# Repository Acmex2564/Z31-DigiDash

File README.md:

# Z31-DigiDash
Reverse Engineering of the 300zx (Z31) Digital Cluster &amp; Design of replacement PCBs

Z31 digital clusters are one of, if not the best examples of this pure 1980s trend. Comprehensive instrumentation, large graphics, and gorgeous VFD illumination were a somewhat expensive option on the 300zx, as well as on Maxima, 240SX, Corvette, Celica/Supra, and a variety of other cars. As the cars languished in the transition period between "late model" and "classic", though, the digital package for the 300zx was not well liked.

It had 3 major issues:

* Terrible update speed
* Lack of brightness
* Unreliability

Now, as Z31s sit at the bottom of the depreciation curve, more people see them as '80s Grand Touring icons and not just as transporation or "sports cars", and a functioning digital dash can be a highlight instead of a detractor.

I have the personal goal of solving at least two of the 3 main problems with these units, by reverse engineering them in the existing state, and designing a drop-on processor board and replacement power supply module. 

See files "Physical Description.md", "Logical Description.md", and "Electrical Description.md" for my observations so far. Also present are images showing how to power up the dash out of the car, and a picture of a printout that I used to map out the input pins.

Note: I am a hobbiest. I am not a EE, CS, Developer, or any related field. Generally, I do my best to read and cargo-cult my way into a working solution. Progress will be slow. The modular design has made it easy to get quick progress and seize control of the actual display, so input, input protection, and power supply will be the main challenges.

Note: None of the boards as-presented are in a state fit to be used without major effort. Big chunks of the Compute-Early-1 design were never tested before I moved on to Compute-Early-2 after component obselecence, etc. and the code to do more than flash the display on the bench was never developed.

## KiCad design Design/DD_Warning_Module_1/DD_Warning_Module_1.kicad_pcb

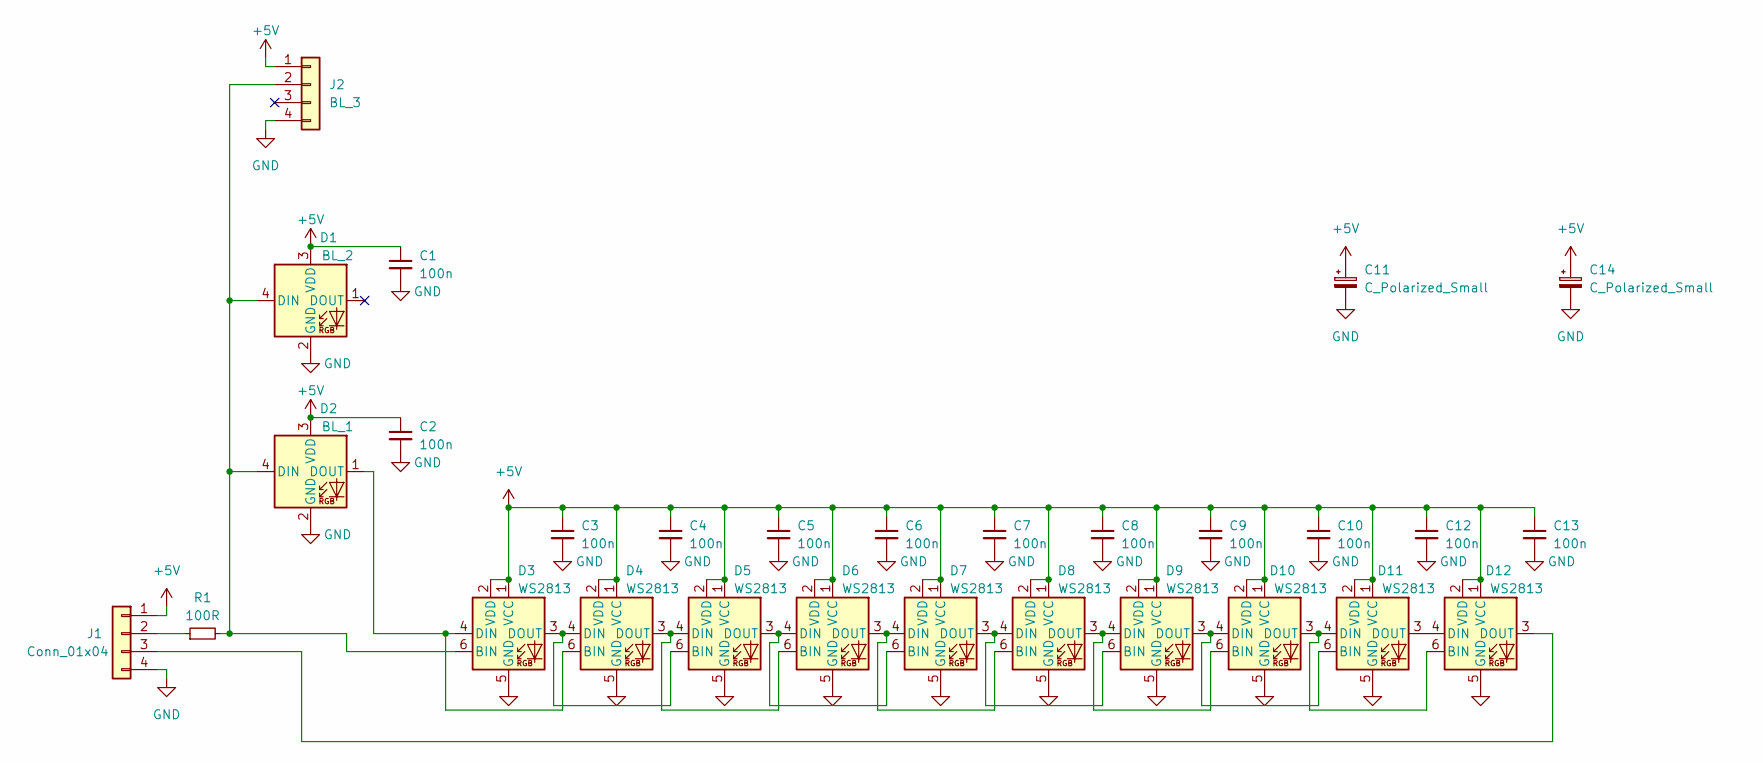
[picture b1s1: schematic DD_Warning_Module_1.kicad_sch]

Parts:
C1, C2, C3, C4, C5, C6, C7, C8, C9, C10, C12, C13: 100n; C_0805_2012Metric_Pad1.18x1.45mm_HandSolder
C11, C14: C_Polarized_Small; CP_Radial_D8.0mm_P2.50mm
D1: BL_2; LED_D5.0mm-4_RGB
D2: BL_1; LED_D5.0mm-4_RGB
D3, D4, D5, D6, D7, D8, D9, D10, D11, D12: WS2813; LED_WS2812_PLCC6_5.0x5.0mm_P1.6mm
J1: Conn_01x04; JST_XH_B4B-XH-A_1x04_P2.50mm_Vertical
J2: BL_3; JST_XH_B4B-XH-A_1x04_P2.50mm_Vertical
R1: 100R; R_0805_2012Metric_Pad1.20x1.40mm_HandSolder

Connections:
+5V: C1.1, C2.1, C3.1, C4.1, C5.1, C6.1, C7.1, C8.1, C9.1, C10.1, C11.1, C12.1, C13.1, C14.1, D1.3 (VDD), D2.3 (VDD), D3.1 (VCC), D3.2 (VDD), D4.1 (VCC), D4.2 (VDD), D5.1 (VCC), D5.2 (VDD), D6.1 (VCC), D6.2 (VDD), D7.1 (VCC), D7.2 (VDD), D8.1 (VCC), D8.2 (VDD), D9.1 (VCC), D9.2 (VDD), D10.1 (VCC), D10.2 (VDD), D11.1 (VCC), D11.2 (VDD), D12.1 (VCC), D12.2 (VDD), J1.1, J2.1
GND: C1.2, C2.2, C3.2, C4.2, C5.2, C6.2, C7.2, C8.2, C9.2, C10.2, C11.2, C12.2, C13.2, C14.2, D1.2 (GND), D2.2 (GND), D3.5 (GND), D4.5 (GND), D5.5 (GND), D6.5 (GND), D7.5 (GND), D8.5 (GND), D9.5 (GND), D10.5 (GND), D11.5 (GND), D12.5 (GND), J1.4, J2.4
unnamed: D1.4 (DIN), D2.4 (DIN), D3.6 (BIN), J2.2, R1.2
unnamed: D2.1 (DOUT), D3.4 (DIN), D4.6 (BIN)
unnamed: D3.3 (DOUT), D4.4 (DIN), D5.6 (BIN)
unnamed: D4.3 (DOUT), D5.4 (DIN), D6.6 (BIN)
unnamed: D5.3 (DOUT), D6.4 (DIN), D7.6 (BIN)
unnamed: D6.3 (DOUT), D7.4 (DIN), D8.6 (BIN)
unnamed: D7.3 (DOUT), D8.4 (DIN), D9.6 (BIN)
unnamed: D8.3 (DOUT), D9.4 (DIN), D10.6 (BIN)
unnamed: D9.3 (DOUT), D10.4 (DIN), D11.6 (BIN)
unnamed: D10.3 (DOUT), D11.4 (DIN), D12.6 (BIN)
unnamed: D11.3 (DOUT), D12.4 (DIN)
unnamed: D12.3 (DOUT), J1.3
unnamed: J1.2, R1.1

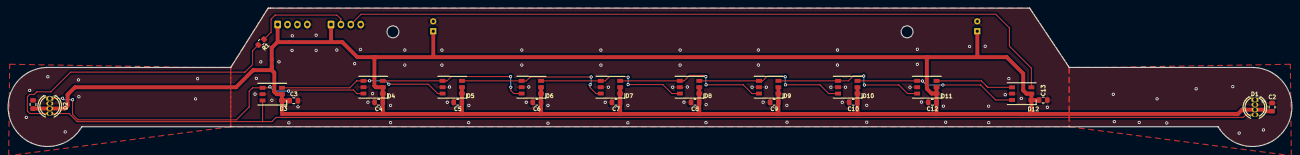
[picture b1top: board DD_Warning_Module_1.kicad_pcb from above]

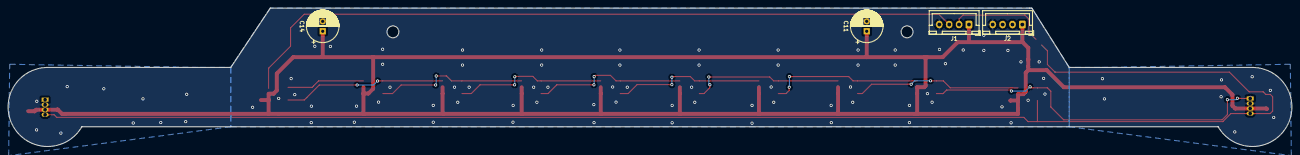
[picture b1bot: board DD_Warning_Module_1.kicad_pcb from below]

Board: 2 copper layers, 324.6 x 35.0 mm, 29 parts (4 on the bottom side), 15 nets.

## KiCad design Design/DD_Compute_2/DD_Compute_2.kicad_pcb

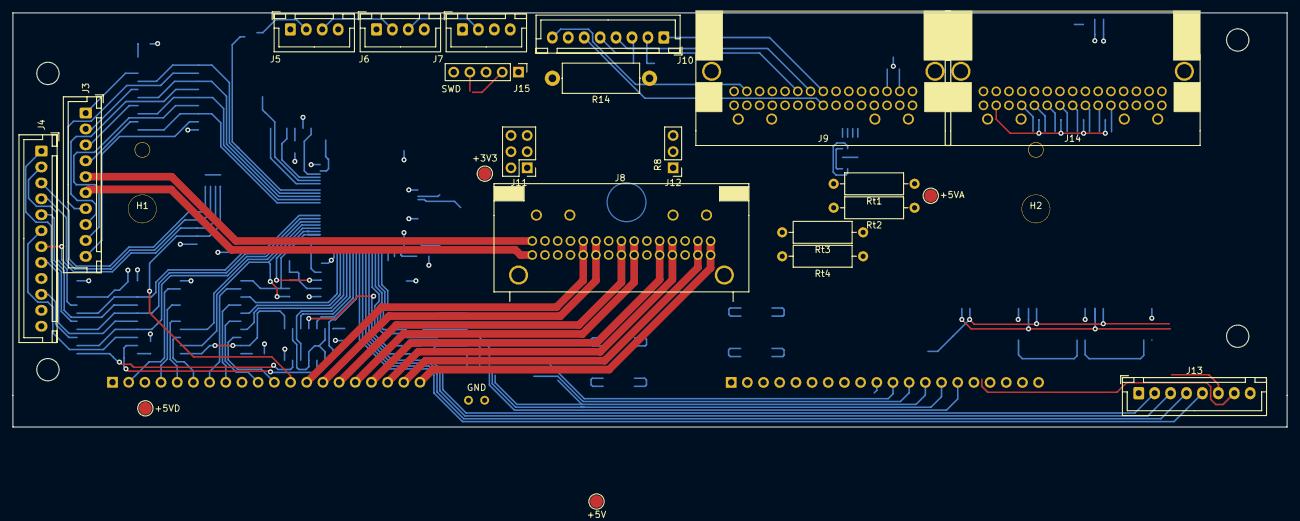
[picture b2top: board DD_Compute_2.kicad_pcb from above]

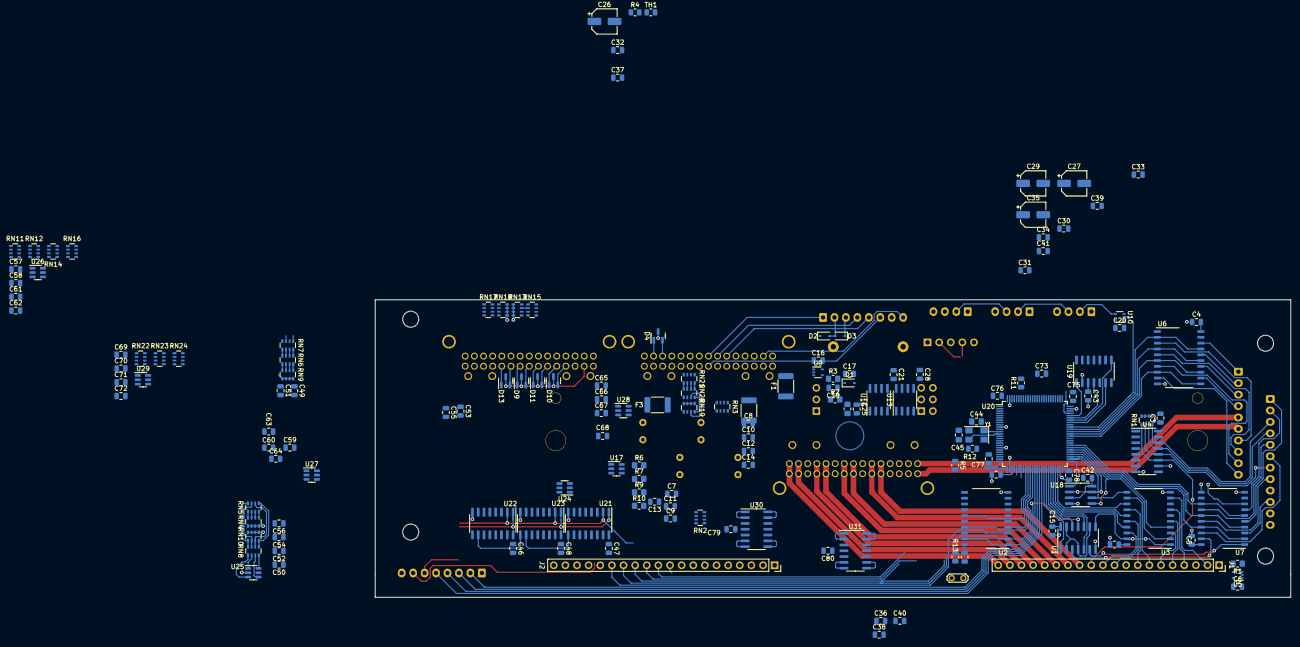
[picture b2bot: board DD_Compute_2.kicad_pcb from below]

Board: 4 copper layers, 200.0 x 65.0 mm, 183 parts (155 on the bottom side), 224 nets.

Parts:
3.3V1: +3V3; TestPoint_Pad_D2.0mm
5V_Analog1: +5VA; TestPoint_Pad_D2.0mm
5V_Disp1: +5VD; TestPoint_Pad_D2.0mm
5V_Logic1: +5V; TestPoint_Pad_D2.0mm
C1, C2, C3, C4, C5, C6, C7, C8, C9, C10, C11, C12, C14, C15, C16, C20, C21, C28, C31, C38, C39, C42, C43, C46, C47, C48, C49, C50, C51, C52, C53, C54, C55, C56, C57, C58, C59, C60, C61, C62, C63, C64, C65, C66, C67, C68, C69, C70, C71, C72, C73, C74, C75, C76, C77, C78, C79, C80: 100nF; C_0805_2012Metric
C13, C17, C19, C25: 10n; C_0805_2012Metric
C26, C27, C29, C35: 47uF; CP_Elec_5x5.3
C30, C32, C34, C36, C37: 1uF; C_0805_2012Metric
C33, C40, C41: 10nF; C_0805_2012Metric
C44, C45: 20pF; C_0805_2012Metric_Pad1.18x1.45mm_HandSolder
D1, D2, D3: 1N4148WS; D_SOD-323
D4: NUP2105L; SOT-23
D9, D10, D11, D13: BAV70; SOT-23
F1, F2, F3: Polyfuse_Small; Fuse_1812_4532Metric_Pad1.30x3.40mm_HandSolder
GND1: GND; TestPoint_2Pads_Pitch2.54mm_Drill0.8mm
H1, H2: Peg; Z31_DD_Mountpeg
H3, H4, H5, H6: Hole; MountingHole_3.5mm
J1: DISP. BOARD CONN 1 (1-20); PinSocket_1x20_P2.54mm_Vertical
J2: DISP. BOARD CONN 2 (21-40); PinSocket_1x20_P2.54mm_Vertical
J3: TRIP BOARD CONN 1 (1-10); JST_XH_B10B-XH-A_1x10_P2.50mm_Vertical
J4: TRIP BOARD CONN 2 (11-22); JST_XH_B12B-XH-A_1x12_P2.50mm_Vertical
J5, J6, J7: Conn_01x03; JST_XH_B4B-XH-A_1x04_P2.50mm_Vertical
J8: POWER SUPPLY - 0349580340; 34958
J9: CAR INTERFACE - 0349610341 - SIG; 349610340
J10: DISP_BOARD_CONN_3; JST_XH_B8B-XH-A_1x08_P2.50mm_Vertical
J11: ISOLATED OUPTUTS & POWER; PinHeader_2x03_P2.54mm_Vertical
J12: ISOLATED INPUTS; PinHeader_1x03_P2.54mm_Vertical
J13: ODOMETER MODULE; JST_XH_B8B-XH-A_1x08_P2.50mm_Vertical
J14: CAR INTERFACE - 0349610341; 349610340
J15: SWD; PinHeader_1x05_P2.54mm_Vertical
R1: 47k; R_0805_2012Metric_Pad1.20x1.40mm_HandSolder
R2: 2.2k; R_0805_2012Metric_Pad1.20x1.40mm_HandSolder
R3, R8: 1k; R_0805_2012Metric_Pad1.20x1.40mm_HandSolder
R4, R5: 47k; R_0805_2012Metric
R6, R9: 75k 1%; R_0805_2012Metric_Pad1.20x1.40mm_HandSolder
R7, R10: 35.7k 1%; R_0805_2012Metric_Pad1.20x1.40mm_HandSolder
R11, R12, R13: 100k; R_0805_2012Metric
R14: 47; R_Axial_DIN0414_L11.9mm_D4.5mm_P15.24mm_Horizontal
RN1, RN2, RN3, RN4, RN5, RN6, RN7, RN8, RN9, RN10, RN11, RN12, RN13, RN14, RN15, RN16, RN17, RN18, RN19, RN20, RN21, RN22, RN23, RN24: 4.7k; R_Array_Convex_4x0603
Rt1, Rt2, Rt3, Rt4: R; R_Axial_DIN0309_L9.0mm_D3.2mm_P12.70mm_Horizontal
TH1: NTCG204AH473JT1; R_0805_2012Metric
U1: 74HCT00D,653; SO-14_3.9x8.65mm_P1.27mm
U2, U3, U6, U7: 74HCT244D,653; SO-20_12.8x7.5mm_P1.27mm
U4, U21, U22, U23: 74HC165D-Q100,118; SOIC-16_3.9x9.9mm_P1.27mm
U5, U9, U10: SN74LV1T34DCK; SOT-353_SC-70-5
U13, U16: VO0631T; SOIC-8_3.9x4.9mm_P1.27mm
U17, U24, U25, U26, U27, U28, U29: SRV05-4; SOT-23-6
U18: 25LC020AT-E/SN; SOIC-8_3.9x4.9mm_P1.27mm
U19: TJR1443; SO-14_3.9x8.65mm_P1.27mm
U20: STM32F103V8Tx; LQFP-100_14x14mm_P0.5mm
U30, U31: LMV324AIDR; SOIC-14_3.9x8.7mm_P1.27mm
Y1: 8MHz; Crystal_SMD_5032-4Pin_5.0x3.2mm

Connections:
12V_Sense: R9.2, R10.1, RN2.2 (R2.1), U17.4 (IO3)
+3V3: 3.3V1.1, C3.1, C21.2, C28.2, C42.2, C46.1, C47.1, C48.1, C73.1, C74.1, C75.1, C76.1, C77.1, C78.1, C79.1, C80.1, J11.2, J15.1, R1.2, R4.1, R12.1, RN1.5 (R4.2), RN1.6 (R3.2), RN1.7 (R2.2), RN1.8 (R1.2), U4.16 (VCC), U13.8 (VCC), U16.8 (VCC), U18.3 (~WP), U18.7 (~HOLD), U18.8 (VCC), U19.5 (Vio), U20.6 (VBAT), U20.11 (VDD), U20.22 (VDDA), U20.28 (VDD), U20.50 (VDD), U20.75 (VDD), U20.100 (VDD), U21.16 (VCC), U22.16 (VCC), U23.16 (VCC), U30.4 (V+), U31.4 (V+)
+5V: 5V_Logic1.1, C1.2, C2.2, C4.2, C5.1, C15.2, C26.1, C29.1, C32.1, C34.1, C43.1, U1.14 (VCC), U2.20 (VCC), U3.20 (VCC), U6.20 (VCC), U7.20 (VCC), U17.5 (VP), U19.3 (Vcc), U24.5 (VP), U25.5 (VP), U26.5 (VP), U27.5 (VP), U28.5 (VP), U29.5 (VP)
+5VA: 5V_Analog1.1, C16.1, C27.1, C30.1, C31.1, C33.1, J9.8, J9.23, J11.3, R3.2, R5.1, R8.2, RN24.3 (R3.1), RN24.4 (R4.1), Rt1.1, Rt2.1, Rt3.1, Rt4.1, U9.5 (VCC)
+5VD: 5V_Disp1.1, C6.1, C20.1, C35.1, C37.1, C39.1, C41.1, J1.3, J2.5, J2.6, J4.9, J5.1, J6.1, J7.1, J8.2, J13.1, U1.2, U1.4, U1.9, U1.13, U5.5 (VCC), U10.5 (VCC)
+12V_ACC_ON: F1.2, J9.4
+12V_CONST: F3.1, J9.1, R9.1
+12V_ON_START: F2.2, J9.3
+12V_ON_START_B: J9.33, J10.8, R14.1
+12V_Security: J9.29, J10.5, RN24.1 (R1.1)
/BOOT0: R11.1, U20.94 (BOOT0)
/CAN_EN: U19.6 (EN), U20.68 (PA9)
/CAN_RX: U19.4 (RXCAN), U20.70 (PA11)
/CAN_TX: U19.1 (TXCAN), U20.71 (PA12)
/DC_ODO: J13.5, U20.41 (PE10)
/Disp_CTL_IC31: J4.6, U7.18 (1Y0)
/Disp_Mode_IC30: J4.10, U7.3 (2Y0)
/Disp_Reset_IC30: J4.1, U7.5 (2Y1)
/Disp_Reset_IC31: J4.8, U7.16 (1Y1)
/Disp_S0_IC30: J3.7, U6.3 (2Y0)
/Disp_S0_IC31: J3.1, U6.18 (1Y0)
/Disp_S1_IC30: J3.8, U6.5 (2Y1)
/Disp_S1_IC31: J3.2, U6.16 (1Y1)
/Disp_S2_IC30: J3.9, U6.7 (2Y2)
/Disp_S2_IC31: J3.3, U6.14 (1Y2)
/Disp_S3_IC30: J3.10, U6.9 (2Y3)
/Disp_S3_IC31: J3.4, U6.12 (1Y3)
/Disp_~WR_IC30: J4.2, U7.7 (2Y2)
/Disp_~WR_IC31: J4.5, U7.14 (1Y2)
/Display_LH_Satellite: J1.10, U3.16 (1Y1)
/Display_SI_Satellite: J1.11, U3.18 (1Y0)
/Display_~CS_Fuel_Lvl: J1.8, U3.14 (1Y2)
/Display_~CS_Fuel_Qty: J1.4, U3.7 (2Y2)
/Display_~CS_Oil: J1.5, U3.5 (2Y1)
/Display_~CS_SpeedGraph: J2.15, U2.3 (2Y0)
/Display_~CS_SpeedNumeric: J2.14, U2.18 (1Y0)
/Display_~CS_TachGraphLoad: J2.12, U2.16 (1Y1)
/Display_~CS_TachGraphRpm: J2.13, U2.5 (2Y1)
/Display_~CS_TachNumeric: J2.11, U2.7 (2Y2)
/Display_~CS_Temp: J1.6, U3.3 (2Y0)
/Display_~CS_Volts: J1.7, U3.12 (1Y3)
/Display_~SCK_Main: J2.16, U2.12 (1Y3)
/Display_~SCK_Satellite: J1.2, U3.9 (2Y3)
/EN_ODO: J13.2, U20.38 (PE7)
/Extra_High_Input: J14.20, RN7.4 (R4.1)
/IC30_OE: U1.1, U20.42 (PE11)
/IC31_OE: U1.5, U20.45 (PE14)
/Illum_Data_Loop1: J5.3, J6.2
/Illum_Data_Loop2: J6.3, J7.2
/Illum_Data_Out: J5.2, U10.4 (Y)
/Indicator_Pilot_Common: J14.5, RN9.5 (R4.2), RN9.6 (R3.2), RN9.7 (R2.2), RN9.8 (R1.2)
/Indicator_Pilot_Left: J14.22, RN7.2 (R2.1)
/Indicator_Pilot_Main: J14.23, RN7.1 (R1.1)
/Indicator_Pilot_Right: J14.21, RN7.3 (R3.1)
/RESET_ODO: J13.4, U20.40 (PE9)
/SPI1_CS0: U2.13 (2A2), U20.33 (PC4)
/SPI1_CS1: U2.15 (2A1), U20.34 (PC5)
/SPI1_CS2/BOOT1: R13.1, U2.2 (1A0), U20.37 (PB2)
/SPI1_CS3: U2.17 (2A0), U20.36 (PB1)
/SPI1_CS4: U2.4 (1A1), U20.35 (PB0)
/SPI1_CS5: U20.29 (PA4), U21.15 (~CE), U22.15 (~CE), U23.15 (~CE)
/SPI1_LH: U21.1 (~PL), U22.1 (~PL), U23.1 (~PL)
/SPI1_MISO: U20.31 (PA6), U22.9 (Q7)
/SPI1_MOSI: J13.7, U20.32 (PA7)
/SPI1_SCK: J13.6, U2.8 (1A3), U20.30 (PA5), U21.2 (CP), U22.2 (CP), U23.2 (CP)
/SPI2_CS0: U3.13 (2A2), U20.48 (PB11)
/SPI2_CS1: U3.15 (2A1), U20.47 (PB10)
/SPI2_CS2: U3.17 (2A0), U20.46 (PE15)
/SWCLK: J15.4, U20.76 (PA14)
/SWDIO: J15.2, U20.72 (PA13)
/Secondary_Warning_Input/ASCD_CruiseB: C66.2, RN19.7 (R2.2), RN20.7 (R2.2), U22.4 (D5), U28.4 (IO3)
/Secondary_Warning_Input/ASCD_OnB: C65.2, RN19.8 (R1.2), RN20.8 (R1.2), U22.3 (D4), U28.6 (IO4)
/Secondary_Warning_Input/ASCD_Set_Disp_1B: C67.2, RN19.6 (R3.2), RN20.6 (R3.2), U22.5 (D6), U28.1 (IO1)
/Secondary_Warning_Input/ASCD_Set_Disp_2B: C68.2, RN19.5 (R4.2), RN20.5 (R4.2), U22.6 (D7), U28.3 (IO2)
/Secondary_Warning_Input/Belt: C50.2, RN8.1 (R1.1), U23.11 (D0), U25.3 (IO2)
/Secondary_Warning_Input/Brake_1: C54.2, RN8.3 (R3.1), U23.13 (D2), U25.4 (IO3)
/Secondary_Warning_Input/Brake_2: C56.2, RN8.4 (R4.1), U23.14 (D3), U25.6 (IO4)
/Secondary_Warning_Input/Coolant: C57.2, RN14.8 (R1.2), U23.3 (D4), U26.3 (IO2)
/Secondary_Warning_Input/Door: C62.2, RN14.5 (R4.2), U23.6 (D7), U26.6 (IO4)
/Secondary_Warning_Input/Extra_HighB: C55.2, RN6.5 (R4.2), RN9.4 (R4.1), U21.3 (D4), U24.3 (IO2)
/Secondary_Warning_Input/Extra_Low_1B: C59.2, RN17.1 (R1.1), U21.11 (D0), U27.3 (IO2)
/Secondary_Warning_Input/Extra_Low_2B: C60.2, RN17.2 (R2.1), U21.12 (D1), U27.1 (IO1)
/Secondary_Warning_Input/Extra_Low_3B: C63.2, RN17.3 (R3.1), U21.13 (D2), U27.4 (IO3)
/Secondary_Warning_Input/Extra_Low_4B: C64.2, RN17.4 (R4.1), U21.14 (D3), U27.6 (IO4)
/Secondary_Warning_Input/Headlamp: C58.2, RN14.7 (R2.2), U23.4 (D5), U26.1 (IO1)
/Secondary_Warning_Input/Left_Turn: C51.2, RN6.7 (R2.2), RN9.2 (R2.1), U21.6 (D7), U24.4 (IO3)
/Secondary_Warning_Input/Main_Beam: C49.2, RN6.8 (R1.2), RN9.1 (R1.1), U21.5 (D6), U24.6 (IO4)
/Secondary_Warning_Input/Right_Turn: C53.2, RN6.6 (R3.2), RN9.3 (R3.1), U21.4 (D5), U24.1 (IO1)
/Secondary_Warning_Input/Sensor: C52.2, RN8.2 (R2.1), U23.12 (D1), U25.1 (IO1)
/Secondary_Warning_Input/Taillamp: C61.2, RN14.6 (R3.2), U23.5 (D6), U26.4 (IO3)
/Secondary_Warning_Input/Warn_ChargeB: C70.2, RN23.7 (R2.2), U22.13 (D2), U29.1 (IO1)
/Secondary_Warning_Input/Warn_FuelB: C71.2, RN23.6 (R3.2), U22.12 (D1), U29.4 (IO3)
/Secondary_Warning_Input/Warn_Oil_PressB: C72.2, RN23.5 (R4.2), U22.11 (D0), U29.6 (IO4)
/Secondary_Warning_Input/Warn_SecurityB: C69.2, RN23.8 (R1.2), U22.14 (D3), U29.3 (IO2)
/Trip_Mode/CTL: U7.2 (1A0), U7.17 (2A0), U20.56 (PD9)
/Trip_Reset: U7.4 (1A1), U7.15 (2A1), U20.57 (PD10)
/Trip_S0: U6.2 (1A0), U6.17 (2A0), U20.65 (PC8)
/Trip_S1: U6.4 (1A1), U6.15 (2A1), U20.64 (PC7)
/Trip_S2: U6.6 (1A2), U6.13 (2A2), U20.63 (PC6)
/Trip_S3: U6.8 (1A3), U6.11 (2A3), U20.62 (PD15)
/Trip_~WR: U7.6 (1A2), U7.13 (2A2), U20.58 (PD11)
/Warning-12V-Supply: J14.6, RN4.1 (R1.1), RN4.2 (R2.1), RN4.3 (R3.1), RN4.4 (R4.1), RN11.1 (R1.1), RN11.2 (R2.1), RN11.3 (R3.1), RN11.4 (R4.1), RN13.1 (R1.1), RN13.2 (R2.1), RN13.3 (R3.1), RN13.4 (R4.1)
/Warning_Belt: D9.1 (A), J14.11, RN5.7 (R2.2), RN8.7 (R2.2), RN10.2 (R2.1)
/Warning_Brake: D13.2 (A), J14.10, RN5.6 (R3.2), RN8.6 (R3.2), RN10.3 (R3.1)
/Warning_Brake_2: D13.1 (A), J14.9, RN5.5 (R4.2), RN8.5 (R4.2), RN10.4 (R4.1)
/Warning_Bulb_Check: D9.3 (K), D10.3 (K), D11.3 (K), D13.3 (K), J14.18
/Warning_Coolant: D11.2 (A), J14.14, RN12.8 (R1.2), RN14.1 (R1.1), RN16.1 (R1.1)
/Warning_Door: D10.2 (A), J14.16, RN12.5 (R4.2), RN14.4 (R4.1), RN16.4 (R4.1)
/Warning_Extra_1: J14.26, RN15.8 (R1.2), RN17.8 (R1.2), RN18.1 (R1.1)
/Warning_Extra_2: J14.27, RN15.7 (R2.2), RN17.7 (R2.2), RN18.2 (R2.1)
/Warning_Extra_3: J14.28, RN15.6 (R3.2), RN17.6 (R3.2), RN18.3 (R3.1)
/Warning_Extra_4: J14.29, RN15.5 (R4.2), RN17.5 (R4.2), RN18.4 (R4.1)
/Warning_Headlamp: D11.1 (A), J14.13, RN12.7 (R2.2), RN14.2 (R2.1), RN16.2 (R2.1)
/Warning_Sensor: D9.2 (A), J14.12, RN5.8 (R1.2), RN8.8 (R1.2), RN10.1 (R1.1)
/Warning_Taillamp: D10.1 (A), J14.15, RN12.6 (R3.2), RN14.3 (R3.1), RN16.3 (R3.1)
/~CAN_ERR: U19.8 (~ERR), U20.69 (PA10)
/~CAN_STB: U19.14 (~STB_N), U20.67 (PA8)
/~CS_ODO: J13.3, U20.39 (PE8)
/~Disp_BI: J1.1, U5.4 (Y)
/~RESET: J15.5, R12.2, U20.14 (NRST)
ASCD_Cruise: J9.13, RN21.3 (R3.1)
ASCD_On: J9.12, J10.6, RN21.4 (R4.1)
ASCD_Set_Disp_1: J9.14, RN21.2 (R2.1)
ASCD_Set_Disp_2: J9.15, RN21.1 (R1.1)
Bias_Grid_Anode: C36.1, C38.1, C40.1, J2.3, J4.11, J8.14, J8.29
Blanking_Control: R1.1, U5.2 (A)
Clock_1_(Time): D4.1 (K), J9.21, U19.13 (CANH)
Clock_2_(Time): D4.2 (K), J9.22, U19.12 (CANL)
Coil_Negative_(Tach): J9.6, J12.2, R2.2
Filament_Fuel_A: J1.19, J8.18, J8.33
Filament_Fuel_B: J1.20, J8.19, J8.34
Filament_Speed_A: J1.17, J8.15, J8.30
Filament_Speed_B: J1.18, J8.16, J8.31
Filament_Sub_A: J1.13, J8.9, J8.24
Filament_Sub_B: J1.14, J8.10, J8.25
Filament_Tach_A: J1.15, J8.12, J8.27
Filament_Tach_B: J1.16, J8.13, J8.28
Filament_Trip_A: J3.5, J8.5
Filament_Trip_B: J3.6, J8.20
Fuel_Gauge_Main: J9.16, RN3.4 (R4.1), Rt1.2
Fuel_Gauge_Sub: J9.17, RN3.3 (R3.1), Rt2.2
Fuel_Injection_Pulse: C19.1, J9.20, J12.3, U13.3 (C2)
Fuel_Injection_Pulse_Protect: J11.5, U13.6 (VO2)
GND: C1.1, C2.1, C3.2, C4.1, C5.2, C6.2, C7.1, C8.1, C9.1, C10.1, C11.1, C12.1, C13.1, C14.1, C15.1, C16.2, C17.2, C20.2, C21.1, C26.2, C27.2, C28.1, C29.2, C30.2, C31.2, C32.2, C33.2, C34.2, C35.2, C36.2, C37.2, C38.2, C39.2, C40.2, C41.2, C42.1, C43.2, C44.2, C45.2, C46.2, C47.2, C48.2, C49.1, C50.1, C51.1, C52.1, C53.1, C54.1, C55.1, C56.1, C57.1, C58.1, C59.1, C60.1, C61.1, C62.1, C63.1, C64.1, C65.1, C66.1, C67.1, C68.1, C69.1, C70.1, C71.1, C72.1, C73.2, C74.2, C75.2, C76.2, C77.2, C78.2, C79.2, C80.2, D1.2 (A), D4.3 (A), GND1.1, J2.1, J2.2, J4.12, J5.4, J6.4, J7.4, J8.1, J8.8, J8.11, J8.17, J8.23, J8.26, J8.32, J9.2, J9.30, J9.32, J10.7, J11.1, J13.8, J15.3, R7.2, R10.2, R11.2, R13.2, RN10.5 (R4.2), RN10.6 (R3.2), RN10.7 (R2.2), RN10.8 (R1.2), RN16.5 (R4.2), RN16.6 (R3.2), RN16.7 (R2.2), RN16.8 (R1.2), RN18.5 (R4.2), RN18.6 (R3.2), RN18.7 (R2.2), RN18.8 (R1.2), RN19.1 (R1.1), RN19.2 (R2.1), RN19.3 (R3.1), RN19.4 (R4.1), RN22.3 (R3.1), RN22.4 (R4.1), TH1.2, U1.7 (GND), U2.10 (GND), U3.10 (GND), U4.3 (D4), U4.4 (D5), U4.5 (D6), U4.6 (D7), U4.8 (GND), U4.10 (DS), U5.3 (GND), U6.10 (GND), U7.8 (1A3), U7.10 (GND), U7.11 (2A3), U9.3 (GND), U10.3 (GND), U13.2 (C1), U13.5 (GND), U16.5 (GND), U17.2 (VN), U18.4 (GND), U19.2 (GND), U20.10 (VSS), U20.19 (VSSA), U20.27 (VSS), U20.49 (VSS), U20.74 (VSS), U20.99 (VSS), U21.8 (GND), U22.8 (GND), U23.8 (GND), U24.2 (VN), U25.2 (VN), U26.2 (VN), U27.2 (VN), U28.2 (VN), U29.2 (VN), U30.11 (V-), U31.11 (V-), Y1.2, Y1.4
INT_TEMP_SENSE: R4.2, TH1.1
Illum_Data: U10.2 (A), U20.66 (PC9)
Illum_Sense: R6.2, R7.1, RN2.3 (R3.1), U17.1 (IO1)
Illumination_2: J9.7, R6.1
Main_Enable: U1.12, U20.43 (PE12)
Manifold_Pressure: J9.11, RN2.4 (R4.1)
unnamed: C17.1, D1.1 (K), R2.1, U13.1 (A1)
unnamed: D2.2 (A), D3.2 (A), J10.2
unnamed: F1.1, J8.3
unnamed: F2.1, J8.4
unnamed: C7.2, RN2.8 (R1.2)
unnamed: C9.2, RN2.7 (R2.2)
unnamed: C11.2, RN2.6 (R3.2)
unnamed: C13.2, RN2.5 (R4.2)
unnamed: C14.2, RN3.8 (R1.2)
unnamed: C12.2, RN3.7 (R2.2)
unnamed: C10.2, RN3.6 (R3.2)
unnamed: C8.2, RN3.5 (R4.2)
unnamed: RN4.8 (R1.2), RN5.1 (R1.1)
unnamed: RN4.7 (R2.2), RN5.2 (R2.1)
unnamed: RN4.6 (R3.2), RN5.3 (R3.1)
unnamed: RN4.5 (R4.2), RN5.4 (R4.1)
unnamed: RN6.1 (R1.1), RN7.8 (R1.2)
unnamed: RN6.2 (R2.1), RN7.7 (R2.2)
unnamed: RN6.3 (R3.1), RN7.6 (R3.2)
unnamed: RN6.4 (R4.1), RN7.5 (R4.2)
unnamed: RN11.8 (R1.2), RN12.1 (R1.1)
unnamed: RN11.7 (R2.2), RN12.2 (R2.1)
unnamed: RN11.6 (R3.2), RN12.3 (R3.1)
unnamed: RN11.5 (R4.2), RN12.4 (R4.1)
unnamed: RN13.8 (R1.2), RN15.1 (R1.1)
unnamed: RN13.7 (R2.2), RN15.2 (R2.1)
unnamed: RN13.6 (R3.2), RN15.3 (R3.1)
unnamed: RN13.5 (R4.2), RN15.4 (R4.1)
unnamed: RN20.1 (R1.1), RN21.8 (R1.2)
unnamed: RN20.2 (R2.1), RN21.7 (R2.2)
unnamed: RN20.3 (R3.1), RN21.6 (R3.2)
unnamed: RN20.4 (R4.1), RN21.5 (R4.2)
unnamed: RN22.5 (R4.2), RN22.8 (R1.2), RN23.1 (R1.1)
unnamed: RN22.2 (R2.1), RN24.7 (R2.2)
unnamed: RN22.6 (R3.2), RN22.7 (R2.2), RN23.2 (R2.1)
unnamed: U1.11, U2.1 (1OE), U2.19 (2OE)
unnamed: U1.8, U3.1 (1OE), U3.19 (2OE)
unnamed: U1.6, U6.1 (1OE), U7.1 (1OE)
unnamed: U1.3, U6.19 (2OE), U7.19 (2OE)
unnamed: C19.2, R3.1, U13.4 (A2)
unnamed: C25.2, R8.1, U16.1 (A1)
unnamed: C44.1, U20.12 (RCC_OSC_IN), Y1.1
unnamed: C45.1, U20.13 (RCC_OSC_OUT), Y1.3
unnamed: U21.9 (Q7), U23.10 (DS)
unnamed: U22.10 (DS), U23.9 (Q7)
unnamed: U30.1, U30.2 (-)
unnamed: U30.6 (-), U30.7
unnamed: U30.8, U30.9 (-)
unnamed: U30.13 (-), U30.14
unnamed: U31.1, U31.2 (-)
unnamed: U31.6 (-), U31.7
unnamed: U31.8, U31.9 (-)
unnamed: U31.13 (-), U31.14
Oil_Pressure: J9.18, RN3.2 (R2.1), Rt3.2
PS_TEMP_SENSE: J8.22, R5.2, RN2.1 (R1.1)
SPI2_CS5: U18.1 (~CS), U20.51 (PB12)
SPI2_LH: U3.4 (1A1), U4.1 (~PL), U20.55 (PD8)
SPI2_MISO: U4.9 (Q7), U18.2 (MISO), U20.53 (PB14)
SPI2_MOSI: U3.2 (1A0), U18.5 (MOSI), U20.54 (PB15)
SPI2_SCK: U3.11 (2A3), U4.2 (CP), U18.6 (SCK), U20.52 (PB13)
SW_Indicated_Spd: J1.12, RN1.1 (R1.1), U4.11 (D0)
SW_MPH-MPG: J4.7, RN1.2 (R2.1), U4.12 (D1)
SW_Trip_A: J4.4, RN1.3 (R3.1), U4.13 (D2)
SW_Trip_B: J4.3, RN1.4 (R4.1), U4.14 (D3)
Satellite_Enable: U1.10, U20.44 (PE13)
Speed_Sensor_In: C25.1, J9.9, J12.1, U16.2 (C1)
Speed_Sensor_Protect: J11.4, U16.7 (VO1)
Speed_Signal_Out: J9.10, U9.4 (Y)
Tach_Protect: J11.6, U13.7 (VO1)
Warning_Charge: D3.1 (K), J9.25, J10.3, R14.2, RN24.2 (R2.1)
Warning_Fuel_Level: D2.1 (K), J9.26, RN23.3 (R3.1), RN24.6 (R3.2)
Warning_Oil_Pressure: J9.27, J10.1, RN23.4 (R4.1), RN24.5 (R4.2)
Warning_Security: J9.28, J10.4, RN22.1 (R1.1), RN24.8 (R1.2)
Water_Temperature: J9.19, RN3.1 (R1.1), Rt4.2

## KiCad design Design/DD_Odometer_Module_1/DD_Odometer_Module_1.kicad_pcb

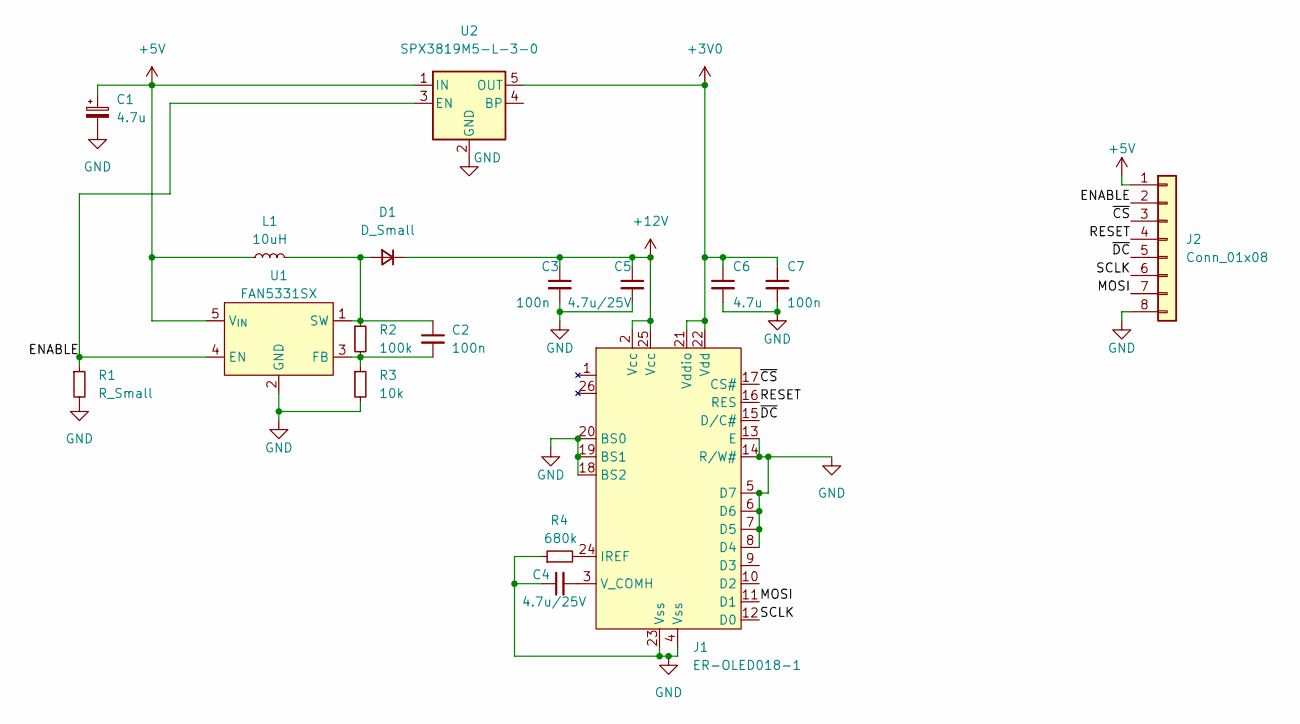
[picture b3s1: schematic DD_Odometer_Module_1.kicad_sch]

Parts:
C1, C6: 4.7u; C_0805_2012Metric_Pad1.18x1.45mm_HandSolder
C2, C3, C7: 100n; C_0805_2012Metric_Pad1.18x1.45mm_HandSolder
C4, C5: 4.7u/25V; C_0805_2012Metric_Pad1.18x1.45mm_HandSolder
D1: D_Small; D_SOD-123
J1: ER-OLED018-1; ER-CON26HT-1
J2: Conn_01x08; JST_XH_B8B-XH-AM_1x08_P2.50mm_Vertical
L1: 10uH; L_1008_2520Metric_Pad1.43x2.20mm_HandSolder
R1: R_Small; R_0805_2012Metric_Pad1.20x1.40mm_HandSolder
R2: 100k; R_0805_2012Metric_Pad1.20x1.40mm_HandSolder
R3: 10k; R_0805_2012Metric_Pad1.20x1.40mm_HandSolder
R4: 680k; R_0805_2012Metric_Pad1.20x1.40mm_HandSolder
U1: FAN5331SX; TSOP-5_1.65x3.05mm_P0.95mm
U2: SPX3819M5-L-3-0; SOT-23-5

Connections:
+3V0: C6.1, C7.1, J1.21 (Vddio), J1.22 (Vdd), U2.5 (OUT)
+5V: C1.1, J2.1, L1.1, U1.5 (V_{IN}), U2.1 (IN)
+12V: C3.1, C5.1, D1.1 (K), J1.2 (Vcc), J1.25 (Vcc)
/ENABLE: J2.2, R1.1, U1.4 (EN), U2.3 (EN)
/MOSI: J1.11 (D1), J2.7
/RESET: J1.16 (RES), J2.4
/SCLK: J1.12 (D0), J2.6
/~CS: J1.17 (CS#), J2.3
/~DC: J1.15 (D/C#), J2.5
GND: C1.2, C3.2, C4.1, C5.2, C6.2, C7.2, J1.4 (Vss), J1.5 (D7), J1.6 (D6), J1.7 (D5), J1.8 (D4), J1.13 (E), J1.14 (R/W#), J1.18 (BS2), J1.19 (BS1), J1.20 (BS0), J1.23 (Vss), J2.8, R1.2, R3.2, R4.1, U1.2 (GND), U2.2 (GND)
unnamed: C2.1, D1.2 (A), L1.2, R2.1, U1.1 (SW)
unnamed: C2.2, R2.2, R3.1, U1.3 (FB)
unnamed: C4.2, J1.3 (V_COMH)
unnamed: J1.24 (IREF), R4.2

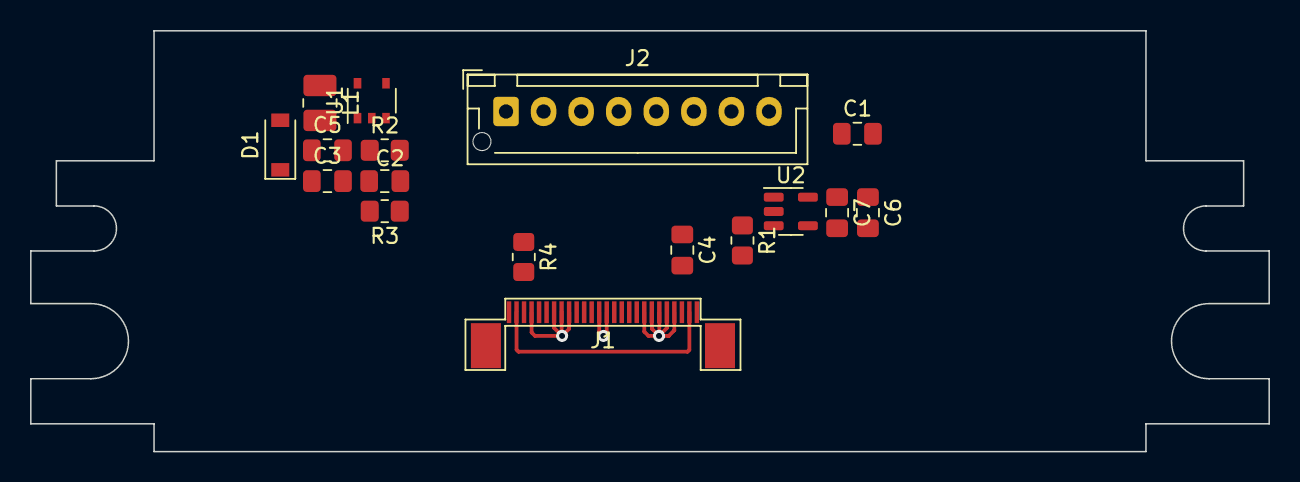
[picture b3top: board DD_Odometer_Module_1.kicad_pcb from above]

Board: 2 copper layers, 82.4 x 28.0 mm, 17 parts (0 on the bottom side), 14 nets.

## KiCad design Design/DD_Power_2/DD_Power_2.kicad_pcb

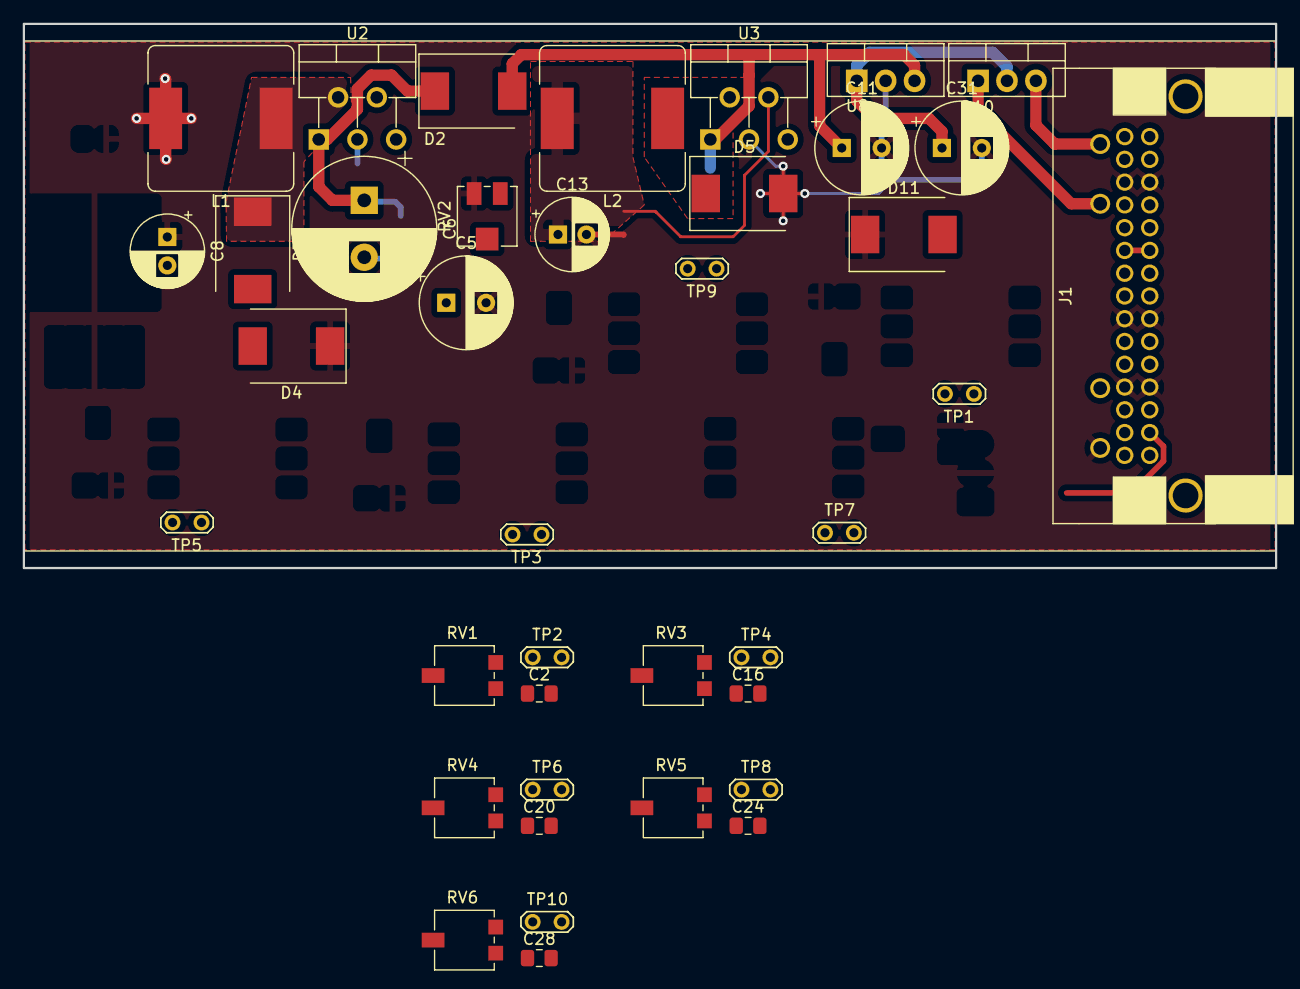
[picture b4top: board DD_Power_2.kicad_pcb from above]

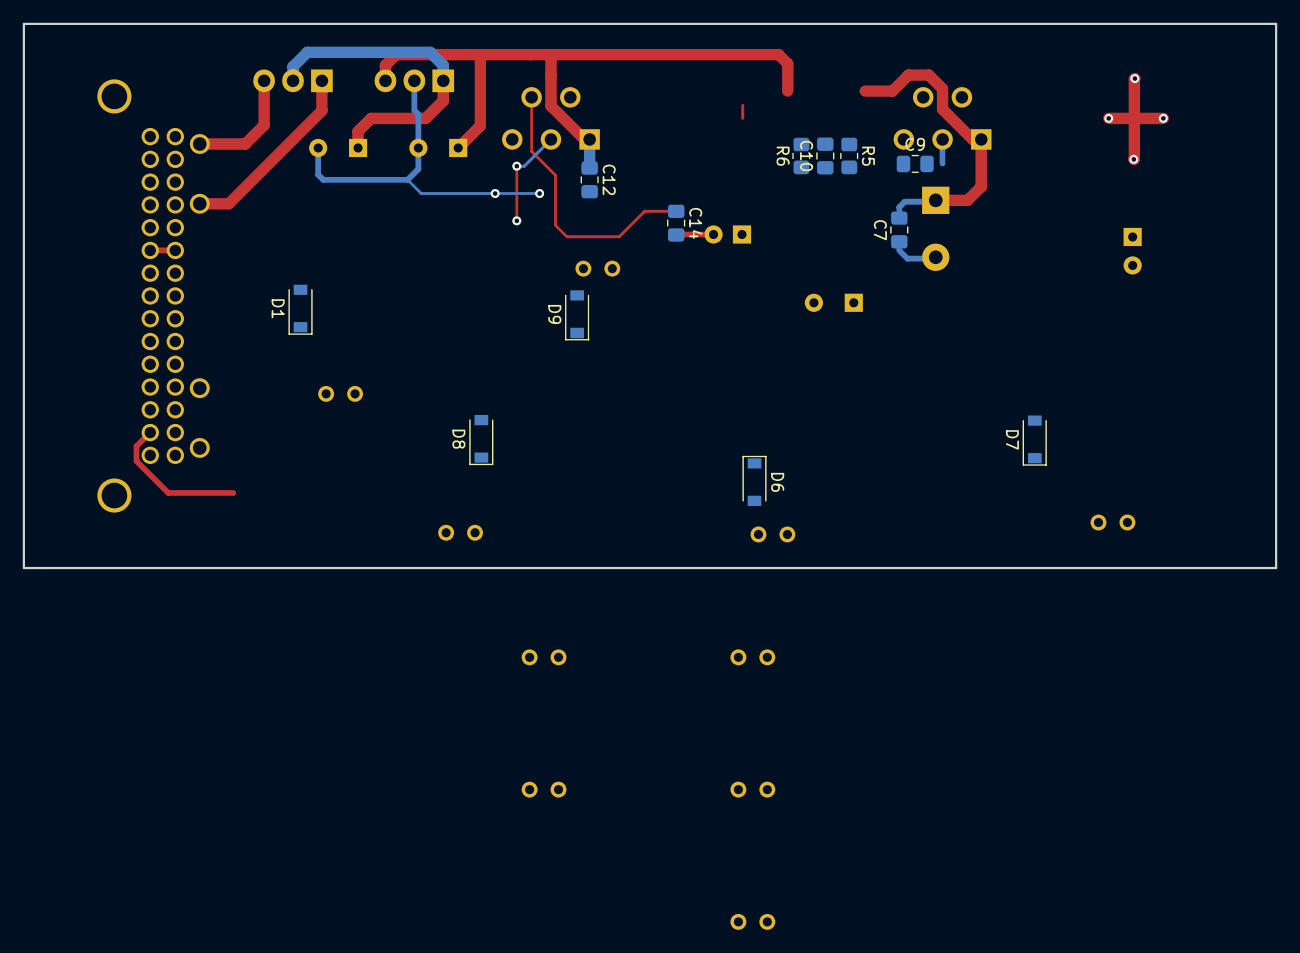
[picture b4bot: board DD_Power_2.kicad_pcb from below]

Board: 2 copper layers, 110.0 x 47.8 mm, 51 parts (12 on the bottom side), 27 nets.

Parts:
C2, C16, C20, C24, C28: 1uF; C_0805_2012Metric_Pad1.18x1.45mm_HandSolder
C5, C11, C31: 100uF 50V; CP_Radial_D8.0mm_P3.50mm
C6: 470uF/50V; CP_Radial_D12.5mm_P5.00mm
C7, C9, C12, C14: C_Small; C_0805_2012Metric_Pad1.18x1.45mm_HandSolder
C8, C13: 220u/25V; CP_Radial_D6.3mm_P2.50mm
C10: 180pF; C_0805_2012Metric_Pad1.18x1.45mm_HandSolder
D1, D6, D7, D8, D9: D_Zener; D_SOD-123
D2, D3, D5: B540C-13-F; D_SMC
D4: 1N5400; D_SMC
D10: MBR20100CT-G1; TO-220-3_Vertical
D11: D_TVS; D_SMC
J1: POWER SUPPLY - 0349610340; 34961
L1, L2: 33uH, 3.5A; L_Bourns_SRR1260
R5: 10k; R_0805_2012Metric_Pad1.20x1.40mm_HandSolder
R6: 1k; R_0805_2012Metric_Pad1.20x1.40mm_HandSolder
RV1, RV3, RV4, RV5, RV6: 10k; Potentiometer_Vishay_TS53YL_Vertical
RV2: 10k; Potentiometer_Vishay_TS53YJ_Vertical
TP1, TP2, TP3, TP4, TP5, TP6, TP7, TP8, TP9, TP10: TestPoint; TestPoint_2Pads_Pitch2.54mm_Drill0.8mm
U2: LM2596T-ADJ; TO-220-5_P3.4x3.7mm_StaggerOdd_Lead3.8mm_Vertical
U3: LM2596T-5; TO-220-5_P3.4x3.7mm_StaggerOdd_Lead3.8mm_Vertical
U8: L7815; TO-220-3_Vertical

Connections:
+5VD: C13.1, C14.1, J1.2, L2.2, U3.4 (FB)
/+12V_2_PROTECT: C11.1, C12.1, D2.2 (A), U3.1 (VIN), U8.3 (OUT)
/+12V_ACC_ON: D10.1 (A), J1.3
/+12V_ON_START: D10.3 (A), J1.4
/-22.5V_BIAS: C6.2, C7.2, C8.2, C9.2, D1.2 (A), D3.2 (A), D4.2 (A), D6.2 (A), D7.2 (A), D8.2 (A), D9.2 (A), J1.14, J1.29, R6.1, U2.3 (GND)
/FILAMENT_01A: J1.33, TP1.1
/FILAMENT_01B: J1.34, TP2.1
/FILAMENT_02A: J1.30, TP4.1
/FILAMENT_02B: J1.31, TP3.1
/FILAMENT_03A: J1.27, TP6.1
/FILAMENT_03B: J1.28, TP5.1
/FILAMENT_04A: J1.24, TP8.1
/FILAMENT_04B: J1.25, TP7.1
/FILAMENT_05A: J1.5, TP10.1
/FILAMENT_05B: J1.20, TP9.1
/Negative Supply/Feedback: C10.2, R5.1, R6.2, U2.4 (FB)
GND: C2.2, C5.2, C8.1, C9.1, C10.1, C11.2, C12.2, C13.2, C14.2, C16.2, C20.2, C24.2, C28.2, C31.2, D4.1 (K), D5.2 (A), D11.1 (A1), J1.1, J1.8, J1.11, J1.17, J1.23, J1.26, J1.32, L1.2, RV2.1, U3.3 (GND), U8.2 (GND)
unnamed: RV1.1, RV1.2
unnamed: C5.1, C6.1, C7.1, D2.1 (K), U2.1 (VIN)
unnamed: RV3.1, RV3.2
unnamed: RV4.1, RV4.2
unnamed: RV5.1, RV5.2
unnamed: RV6.1, RV6.2
unnamed: C31.1, D10.2 (K), D11.2 (A2), U8.1 (IN)
unnamed: D3.1 (K), L1.1, U2.2 (OUT)
unnamed: D5.1 (K), L2.1, U3.2 (OUT)
unnamed: R5.2, RV2.2, RV2.3
